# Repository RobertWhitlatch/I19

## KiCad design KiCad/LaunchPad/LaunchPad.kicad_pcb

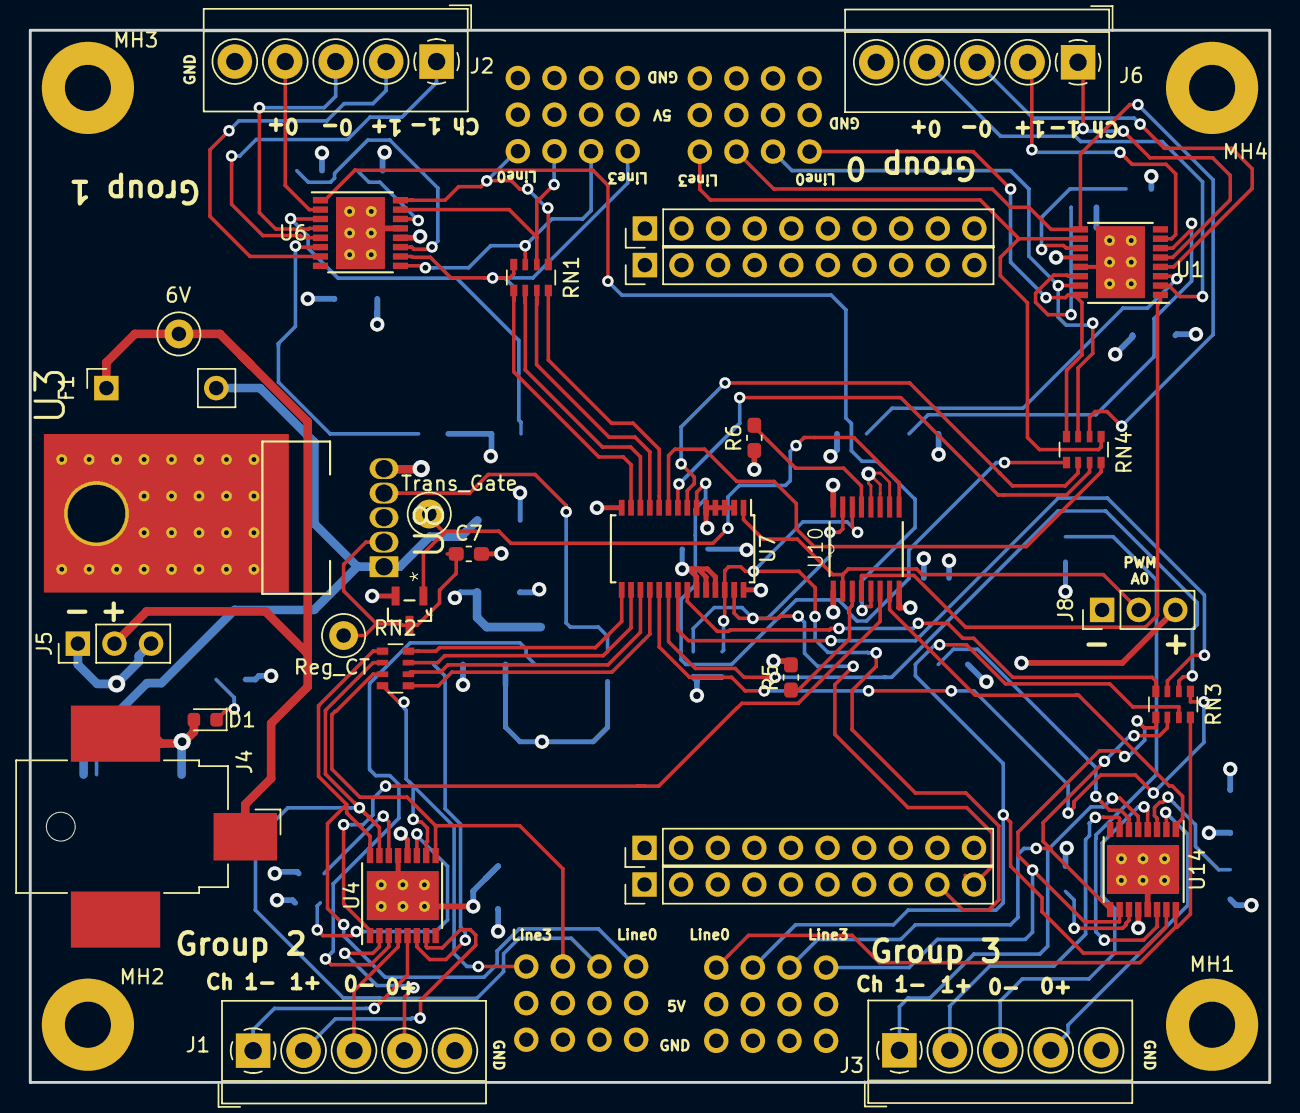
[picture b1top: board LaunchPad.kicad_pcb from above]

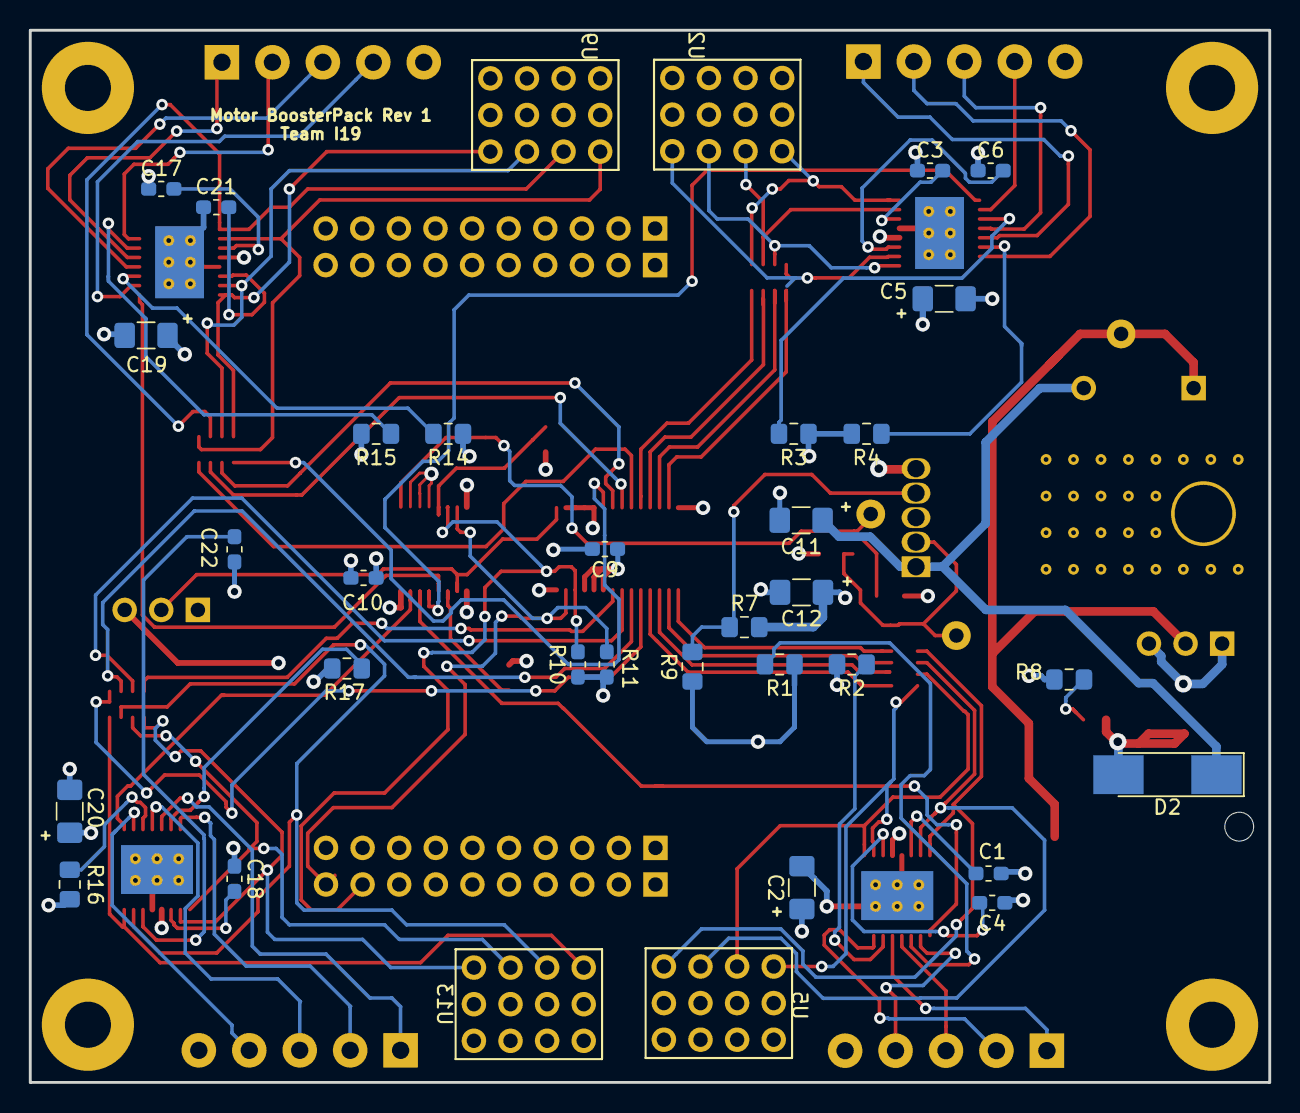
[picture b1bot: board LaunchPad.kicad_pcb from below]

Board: 4 copper layers, 86.0 x 73.0 mm, 69 parts (34 on the bottom side), 82 nets.

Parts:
6V: TestPoint; TestPoint_Loop_D2.50mm_Drill1.0mm_LowProfile
C1, C3, C22: 2.2uF, 6.3V; C_0603_1608Metric_Pad1.05x0.95mm_HandSolder
C2, C5, C12, C19, C20: 10uF, 16V; C_1206_3216Metric_Pad1.42x1.75mm_HandSolder
C4, C6, C17, C18: .01uF, 16V; C_0603_1608Metric_Pad1.05x0.95mm_HandSolder
C7: 2.2pF, 6V; C_0603_1608Metric_Pad1.05x0.95mm_HandSolder
C9: .1uF; C_0603_1608Metric_Pad1.05x0.95mm_HandSolder
C10: .1uF, 10V; C_0603_1608Metric_Pad1.05x0.95mm_HandSolder
C11: 10uf, 16V; C_1206_3216Metric_Pad1.42x1.75mm_HandSolder
C21: 2.2uf, 6.3V; C_0603_1608Metric_Pad1.05x0.95mm_HandSolder
D1: LED; LED_0603_1608Metric
D2: D_Zener; D_MELF_Handsoldering
F1: Fuse; PinSocket_1x02_P2.54mm_Vertical_Custom
H1, H2, H3, H4: Conn_01x10_Male; PinHeader_1x10_P2.54mm_Vertical
J1, J2, J3, J6: Screw_Terminal_01x05; TerminalBlock_4Ucon_1x05_P3.50mm_Horizontal
J4: Barrel_Jack; BarrelJack_CUI_PJ-036AH-SMT_Horizontal
J5: Power_Conn; PinHeader_1x03_P2.54mm_Vertical
J8: Conn_01x03_Female; PinHeader_1x03_P2.54mm_Vertical
MH1, MH2, MH3, MH4: MountingHole; MountingHole_3.2mm_M3_Pad
R1, R2, R3, R4, R16, R17: .130ohms; R_0805_2012Metric_Pad1.15x1.40mm_HandSolder
R5, R6, R10, R11: 2.2K; R_0603_1608Metric_Pad1.05x0.95mm_HandSolder
R7: 50K; R_0805_2012Metric_Pad1.15x1.40mm_HandSolder
R8: 220 ohm; R_0805_2012Metric_Pad1.15x1.40mm_HandSolder
R9: 150K; R_0805_2012Metric_Pad1.15x1.40mm_HandSolder
R14: .13Ohms; R_0805_2012Metric_Pad1.15x1.40mm_HandSolder
R15: .13ohms; R_0805_2012Metric_Pad1.15x1.40mm_HandSolder
RN1, RN2, RN3, RN4: RESISTOR.NETWORK-_4_220; R_Array_Convex_4x0603
Reg_CT: TestPoint; TestPoint_Loop_D2.50mm_Drill1.0mm_LowProfile
Trans_Gate: TestPoint; TestPoint_Loop_D2.50mm_Drill1.0mm_LowProfile
U1, U4, U6, U14: DRV8833PWP; HTSSOP-16-1EP_4.4x5mm_P0.65mm_EP3.4x5mm_Mask2.46x2.31mm_The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
U2, U5, U9, U13: Conn_03x04_Female; Conn_3x4
U3: UCC283-ADJ; TO170P470X1016X2092-5P-SMD
U7: PCA9685PW; TSSOP-28_4.4x9.7mm_P0.65mm
U8: BSS138Q-7-F; SOT95P240X110-3N
U10: TCA6408APWR; SOP65P640X120-16N

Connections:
+3V3: C9.2, C10.1, H1.1, J8.3, R5.2, R6.1, R10.1, R11.1, U7.28, U10.1, U10.16
+5V: C2.1, C4.1, C5.1, C6.1, C12.1, C17.1, C18.1, C19.1, C20.1, R7.2, R8.1, U1.12, U2.5, U2.6, U2.7, U2.8, U3.5, U4.12, U5.5, U5.6, U5.7, U5.8, U6.12, U9.5, U9.6, U9.7, U9.8, U13.5, U13.6, U13.7, U13.8, U14.12
+6V: 6V.1, F1.1, J4.1, J5.2
/GPIO_P0: U1.1, U10.4
/GPIO_P1: U6.1, U10.5
/GPIO_P2: U4.1, U10.6
/GPIO_P3: U10.7, U14.1
/PMW5: RN1.7, U7.11
/PWM0: RN4.1, U7.6
/PWM1: RN4.2, U7.7
/PWM2: RN4.3, U7.8
/PWM3: RN4.4, U7.9
/PWM4: RN1.8, U7.10
/PWM6: RN1.6, U7.12
/PWM7: RN1.5, U7.13
/PWM8: RN2.8, U7.15
/PWM9: RN2.7, U7.16
/PWM10: RN2.6, U7.17
/PWM11: RN2.5, U7.18
/PWM12: RN3.1, U7.19
/PWM13: RN3.2, U7.20
/PWM14: RN3.3, U7.21
/PWM15: RN3.4, U7.22
/U1_AIN1: RN4.8, U1.16, U9.1
/U1_AIN2: RN4.7, U1.15, U9.2
/U1_BIN1: RN4.6, U1.9, U9.3
/U1_BIN2: RN4.5, U1.10, U9.4
/U4_AIN1: RN2.1, U4.16, U5.9
/U4_AIN2: RN2.2, U4.15, U5.10
/U4_BIN1: RN2.3, U4.9, U5.11
/U4_BIN2: RN2.4, U4.10, U5.12
/U6_AIN1: RN1.1, U2.9, U6.16
/U6_AIN2: RN1.2, U2.10, U6.15
/U6_BIN1: RN1.3, U2.11, U6.9
/U6_BIN2: RN1.4, U2.12, U6.10
/U14_AIN1: RN3.8, U13.1, U14.16
/U14_AIN2: RN3.7, U13.2, U14.15
/U14_BIN1: RN3.6, U13.3, U14.9
/U14_BIN2: RN3.5, U13.4, U14.10
A0: J8.2, U7.1, U10.2
GND: C1.1, C2.2, C3.1, C5.2, C7.2, C9.1, C10.2, C11.2, C12.2, C19.2, C20.2, C21.1, C22.1, D1.2, D2.2, H2.2, J1.5, J2.5, J3.5, J4.2, J5.1, J5.3, J6.5, J8.1, R1.1, R2.2, R3.1, R4.2, R9.1, R14.1, R15.2, R16.1, R17.2, U1.13, U1.17, U2.1, U2.2, U2.3, U2.4, U3.3, U3.6, U4.13, U4.17, U5.1, U5.2, U5.3, U5.4, U6.13, U6.17, U7.2, U7.3, U7.4, U7.5, U7.14, U7.23, U7.24, U7.25, U8.2, U9.9, U9.10, U9.11, U9.12, U10.8, U10.10, U10.11, U10.12, U13.9, U13.10, U13.11, U13.12, U14.13, U14.17
I2C_CLK: H1.9, R10.2, U7.26, U10.14
I2C_DATA: H1.10, R11.2, U7.27, U10.15
unnamed: C1.2, U4.14
unnamed: C3.2, U6.14
unnamed: C4.2, U4.11
unnamed: C6.2, U6.11
unnamed: C17.2, U1.11
unnamed: C18.2, U14.11
unnamed: C21.2, U1.14
unnamed: C22.2, U14.14
unnamed: D1.1, R8.2
unnamed: J1.1, U4.5
unnamed: J1.2, U4.7
unnamed: J1.3, U4.4
unnamed: J1.4, U4.2
unnamed: J2.1, U6.5
unnamed: J2.2, U6.7
unnamed: J2.3, U6.4
unnamed: J2.4, U6.2
unnamed: J3.1, U14.5
unnamed: J3.2, U14.7
unnamed: J3.3, U14.4
unnamed: J3.4, U14.2
unnamed: J6.1, U1.5
unnamed: J6.2, U1.7
unnamed: J6.3, U1.4
unnamed: J6.4, U1.2
unnamed: R1.2, U4.3
unnamed: R2.1, U4.6
unnamed: R3.2, U6.3
unnamed: R4.1, U6.6
unnamed: R5.1, U10.3
unnamed: R6.2, U10.13
unnamed: R14.2, U1.3
unnamed: R15.1, U1.6
unnamed: R16.2, U14.3
unnamed: R17.1, U14.6
Reg_ADJ: R7.1, R9.2, U3.4
Reg_CT: C7.1, Reg_CT.1, U3.2, U8.3
Trans_Gate: Trans_Gate.1, U8.1, U10.9
Vin: C11.1, D2.1, F1.2, U3.1

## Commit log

2019-04-15 Moved from BeagleBone Black Wireless due to reliability issues.
2019-04-16 The rest of the initial move.
2019-04-18 Enhance Python Library thanks to insights garnered from MSP432 Library. Console Demo coded, awaiting testing.
2019-04-20 Remote Software complete.
2019-04-21 All Software packages Complete!
